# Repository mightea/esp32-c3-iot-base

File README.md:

# esp32-iot-base

ESP32-WROOM-32E based IoT development board for [ESPHome](https://esphome.io/) designed with [KiCad EDA](https://www.kicad.org/)

<p style="background-color:yellow">
<font color="black"> ⚠️  Work in progress...</font>
</p>

## Project Status

This board is still in it's early design phase...

- [x] Design basic PCB layout
- [x] Generate fabrication data
- [x] Fabicate prototypes
- [ ] Test prototypes (rev. 0.2)

The intention was to use the ESP32-C3 SOC but arduino and esphome support for this generation of chips currently in an early stage and therfore the ESP32-WROOM-32E is used in the meantime.

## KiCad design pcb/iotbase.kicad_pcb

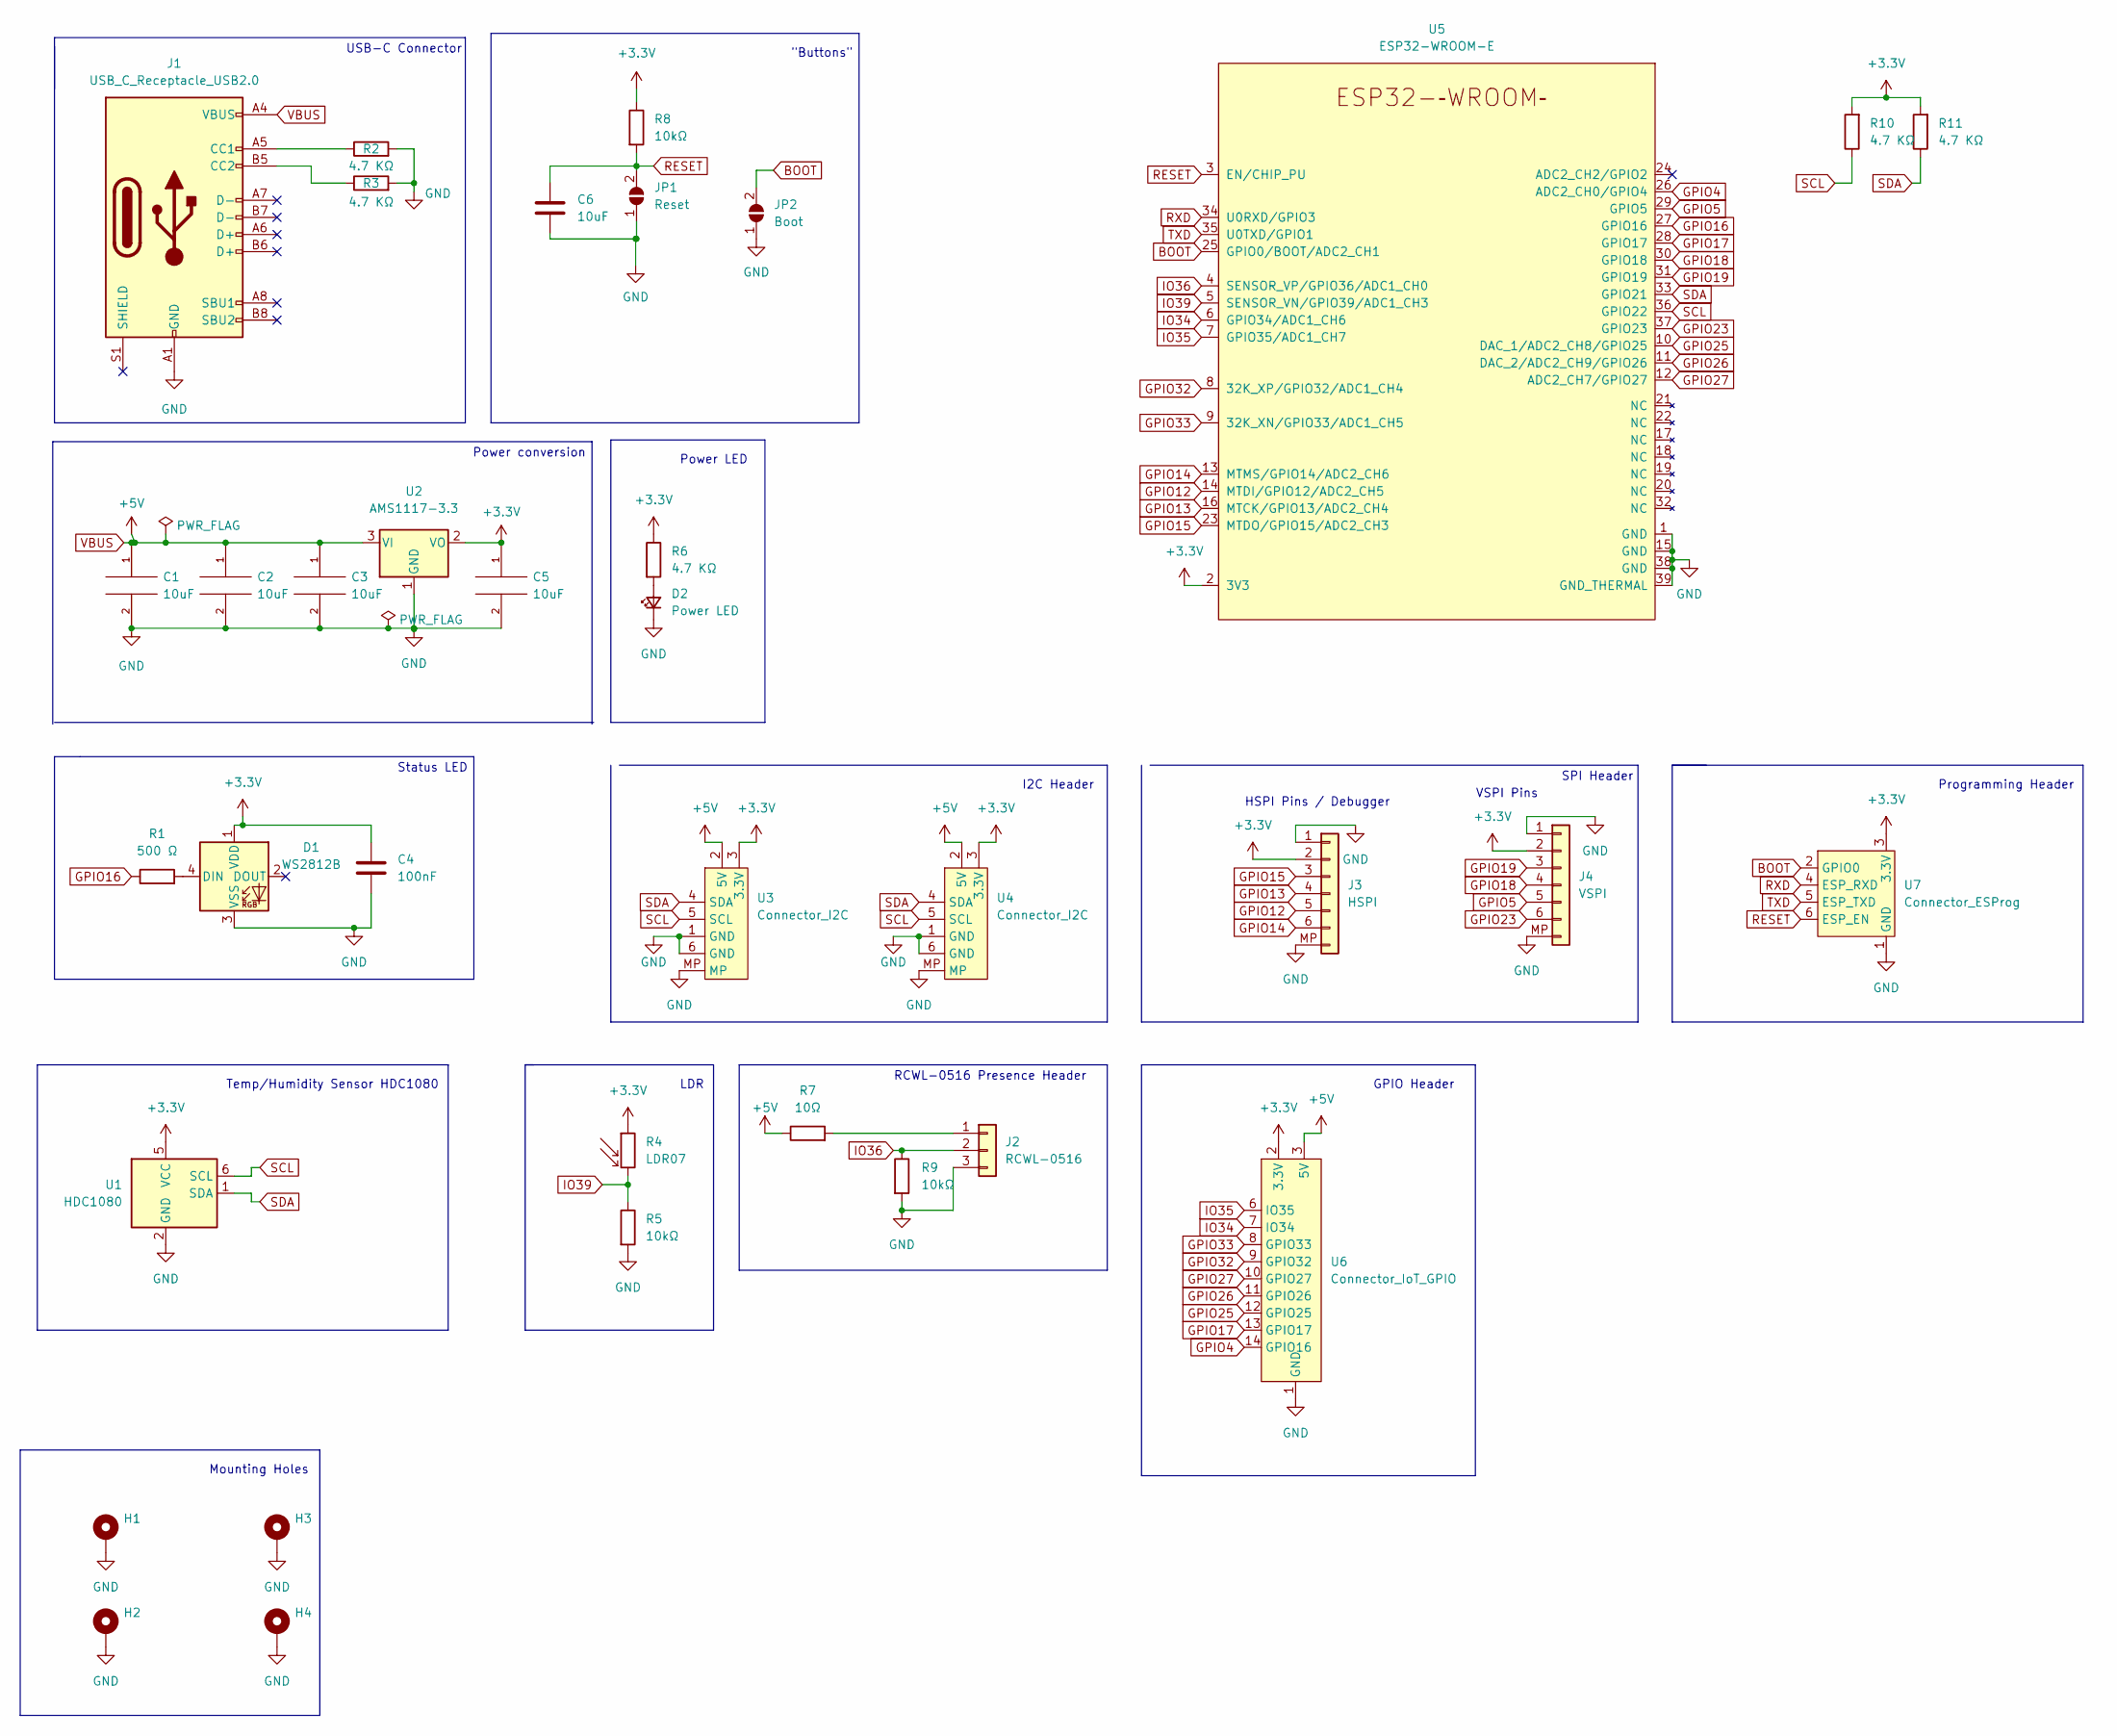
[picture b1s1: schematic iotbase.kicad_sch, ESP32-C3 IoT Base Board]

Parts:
C1, C2, C3, C5, C6: 10uF; C_0603_1608Metric
C4: 100nF; C_0603_1608Metric
D1: WS2812B; LED_WS2812B_PLCC4_5.0x5.0mm_P3.2mm
D2: Power LED; LED_0603_1608Metric
H1, H2, H3, H4: MountingHole_Pad; MountingHole_2.2mm_M2_Pad
J1: USB_C_Receptacle_USB2.0; USB_C_Receptacle_HRO_TYPE-C-31-M-12
J2: RCWL-0516; PinHeader_1x03_P2.54mm_Vertical
J3: HSPI; JST_SH_BM06B-SRSS-TB_1x06-1MP_P1.00mm_Vertical
J4: VSPI; JST_SH_BM06B-SRSS-TB_1x06-1MP_P1.00mm_Vertical
JP1: Reset; SolderJumper-2_P1.3mm_Open_RoundedPad1.0x1.5mm
JP2: Boot; SolderJumper-2_P1.3mm_Open_RoundedPad1.0x1.5mm
R1: 500 Ω; R_0603_1608Metric
R2, R3, R10, R11: 4.7 KΩ; R_0603_1608Metric
R4: LDR07; R_LDR_5.1x4.3mm_P3.4mm_Vertical
R5, R8, R9: 10kΩ; R_0603_1608Metric
R6: 4.7 KΩ; R_0603_1608Metric; jlcpcb C25905
R7: 10Ω; R_0603_1608Metric
U1: HDC1080; Texas_PWSON-N6
U2: AMS1117-3.3; SOT-223-3_TabPin2
U3, U4: Connector_I2C; JST_SH_BM06B-SRSS-TB_1x06-1MP_P1.00mm_Vertical
U5: ESP32-WROOM-E; ESP32-WROOM-32E
U6: Connector_IoT_GPIO
U7: Connector_ESProg; Tag-Connect_TC2030-IDC-FP_2x03_P1.27mm_Vertical

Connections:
+3V3: C4.1, C5.1, D1.1 (VDD), J3.2, J4.2, R4.1, R6.1, R8.1, R10.2, R11.2, U1.5 (VCC), U2.2 (VO), U3.3 (3.3V), U4.3 (3.3V), U5.2 (3V3), U6.2 (3.3V), U7.3 (3.3V)
BOOT: JP2.2 (B), U5.25 (GPIO0/BOOT/ADC2_CH1), U7.2 (GPIO0)
GND: C1.2, C2.2, C3.2, C4.2, C5.2, C6.2, D1.3 (VSS), D2.1 (K), H1.1, H2.1, H3.1, H4.1, J1.A1 (GND), J1.A12 (GND), J1.B1 (GND), J1.B12 (GND), J2.3, J3.1, J3.MP, J4.1, J4.MP, JP1.1 (A), JP2.1 (A), R2.2, R3.2, R5.2, R9.2, U1.2 (GND), U2.1 (GND), U3.1 (GND), U3.6 (GND), U3.MP, U4.1 (GND), U4.6 (GND), U4.MP, U5.1 (GND), U5.15 (GND), U5.38 (GND), U5.39 (GND_THERMAL), U6.1 (GND), U7.1 (GND)
GPIO4: U5.26 (ADC2_CH0/GPIO4), U6.14 (GPIO16)
GPIO5: J4.5, U5.29 (GPIO5)
GPIO12: J3.5, U5.14 (MTDI/GPIO12/ADC2_CH5)
GPIO13: J3.4, U5.16 (MTCK/GPIO13/ADC2_CH4)
GPIO14: J3.6, U5.13 (MTMS/GPIO14/ADC2_CH6)
GPIO15: J3.3, U5.23 (MTDO/GPIO15/ADC2_CH3)
GPIO16: R1.1, U5.27 (GPIO16)
GPIO17: U5.28 (GPIO17), U6.13 (GPIO17)
GPIO18: J4.4, U5.30 (GPIO18)
GPIO19: J4.3, U5.31 (GPIO19)
GPIO23: J4.6, U5.37 (GPIO23)
GPIO25: U5.10 (DAC_1/ADC2_CH8/GPIO25), U6.12 (GPIO25)
GPIO26: U5.11 (DAC_2/ADC2_CH9/GPIO26), U6.11 (GPIO26)
GPIO27: U5.12 (ADC2_CH7/GPIO27), U6.10 (GPIO27)
GPIO32: U5.8 (32K_XP/GPIO32/ADC1_CH4), U6.9 (GPIO32)
GPIO33: U5.9 (32K_XN/GPIO33/ADC1_CH5), U6.8 (GPIO33)
IO34: U5.6 (GPIO34/ADC1_CH6), U6.7 (IO34)
IO35: U5.7 (GPIO35/ADC1_CH7), U6.6 (IO35)
IO36: J2.2, R9.1, U5.4 (SENSOR_VP/GPIO36/ADC1_CH0)
IO39: R4.2, R5.1, U5.5 (SENSOR_VN/GPIO39/ADC1_CH3)
unnamed: D1.4 (DIN), R1.2
unnamed: D2.2 (A), R6.2
unnamed: J1.A5 (CC1), R2.1
unnamed: J1.B5 (CC2), R3.1
unnamed: J2.1, R7.2
RESET: C6.1, JP1.2 (B), R8.2, U5.3 (EN/CHIP_PU), U7.6 (ESP_EN)
RXD: U5.34 (U0RXD/GPIO3), U7.4 (ESP_RXD)
SCL: R10.1, U1.6 (SCL), U3.5 (SCL), U4.5 (SCL), U5.36 (GPIO22)
SDA: R11.1, U1.1 (SDA), U3.4 (SDA), U4.4 (SDA), U5.33 (GPIO21)
TXD: U5.35 (U0TXD/GPIO1), U7.5 (ESP_TXD)
VBUS: C1.1, C2.1, C3.1, J1.A4 (VBUS), J1.A9 (VBUS), J1.B4 (VBUS), J1.B9 (VBUS), R7.1, U2.3 (VI), U3.2 (5V), U4.2 (5V), U6.3 (5V)

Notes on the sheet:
Power LED
HSPI Pins / Debugger
Temp/Humidity Sensor HDC1080
Mounting Holes
Programming Header
I2C Header
USB-C Connector
VSPI Pins
"Buttons"
RCWL-0516 Presence Header
LDR
Power conversion
Status LED
SPI Header
GPIO Header

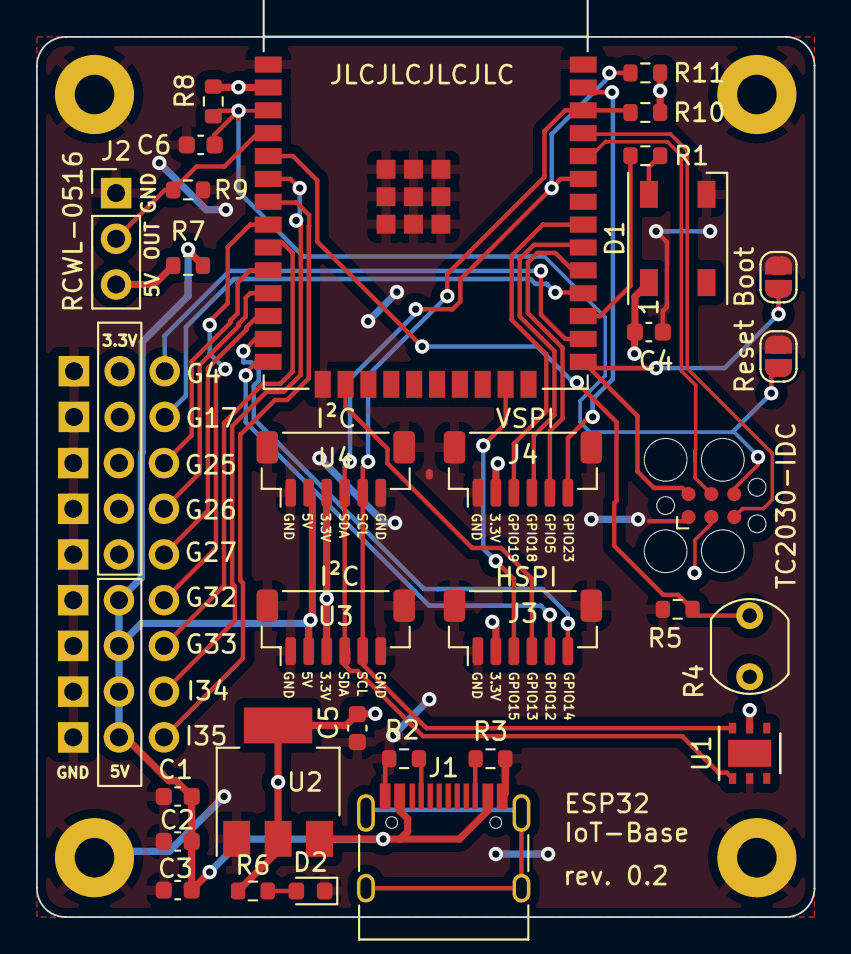
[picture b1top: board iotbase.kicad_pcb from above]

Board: 2 copper layers, 43.2 x 48.9 mm, 36 parts (0 on the bottom side), 34 nets.

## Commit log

2022-04-06 initial import
2022-04-08 adds additionals sensors and connectors
2022-04-08 header update
2022-04-08 renames symbol and footprint libraries
2022-04-08 updates board layout adds header for RCWL-0516 updates readme
2022-04-08 routing and repositioning
2022-04-08 additional routing
2022-04-12 updates gpio connector adds additional traces adds jlcpcb fab plugin
2022-05-01 updates routes
2022-05-04 updates additional routes
2022-05-10 updated components and layout.
2022-05-11 adds rounded corners adds connector pin silkscreens
2022-05-11 updates readme
2022-05-11 updates antenna area cutout adds jlcpcb label
2022-05-14 reorganized repo 🏗
2022-05-20 connects WS2812 led to 3.3v, fixes #3
2022-05-25 fixes boot issues by updating C5 to 10uf
2022-05-28 reduced pcb size added header for RCWL-0516 removed BME280 to save on cost replaced buttons with solder pads
2022-05-28 fixes drc warnings ads rounded corners to rev.2 updates changelog
2022-05-28 updates jlcpcb compoent id's
2022-05-28 release rev. 0.2
2022-05-30 updated the readme

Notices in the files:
pcb/iotbase.kicad_pcb:
© 2022
